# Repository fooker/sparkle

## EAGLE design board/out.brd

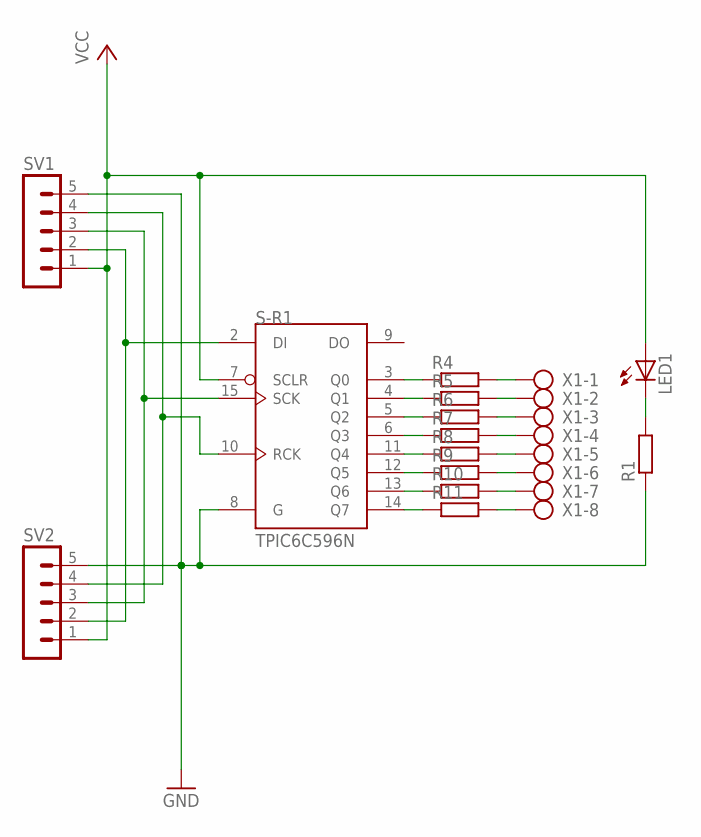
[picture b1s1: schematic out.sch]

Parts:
LED1: LED3MM
R1, R4, R5, R6, R7, R8, R9, R10, R11: R-EU_0207/2V; 0207/2V
S-R1: TPIC6C596N; DIL16
SV1, SV2: MA05-1
X1: AK500/8-H

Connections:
GND: R1.1, S-R1.8 (G), S-R1.16 (GND), SV1.5, SV2.5
unnamed: LED1.K (C), R1.2
unnamed: S-R1.2 (DI), SV1.2, SV2.2
unnamed: S-R1.10 (RCK), SV1.4, SV2.4
unnamed: S-R1.15 (SCK), SV1.3, SV2.3
unnamed: R4.1, S-R1.3 (Q0)
unnamed: R5.1, S-R1.4 (Q1)
unnamed: R6.1, S-R1.5 (Q2)
unnamed: R7.1, S-R1.6 (Q3)
unnamed: R8.1, S-R1.11 (Q4)
unnamed: R9.1, S-R1.12 (Q5)
unnamed: R10.1, S-R1.13 (Q6)
unnamed: R11.1, S-R1.14 (Q7)
unnamed: R4.2, X1.1
unnamed: R5.2, X1.2
unnamed: R6.2, X1.3
unnamed: R7.2, X1.4
unnamed: R8.2, X1.5
unnamed: R9.2, X1.6
unnamed: R10.2, X1.7
unnamed: R11.2, X1.8
VCC: LED1.A, S-R1.1 (VCC), S-R1.7 (SCLR), SV1.1, SV2.1

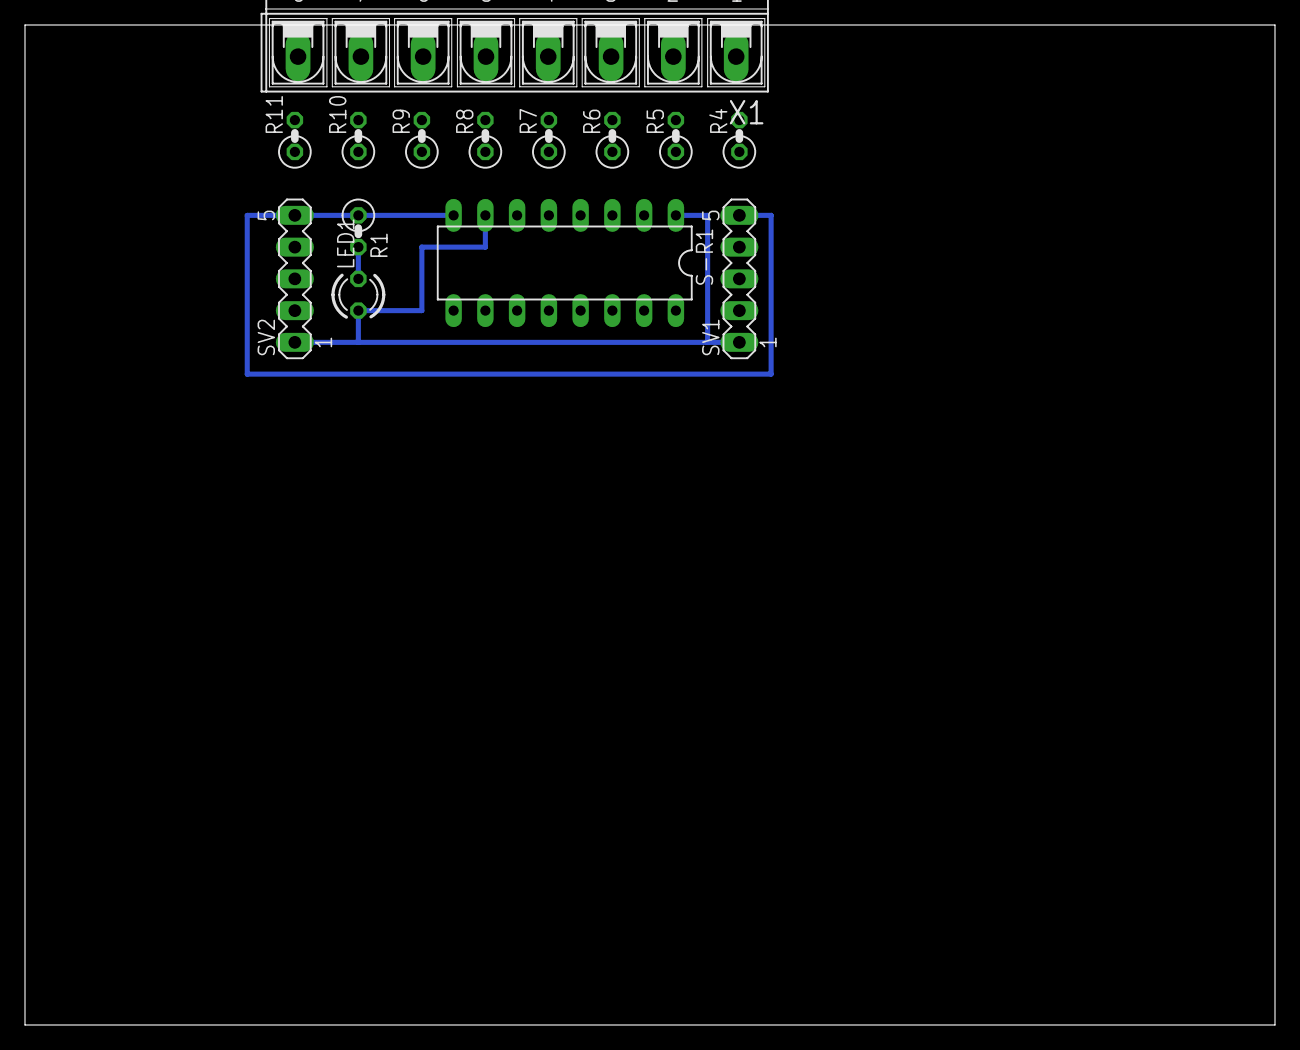
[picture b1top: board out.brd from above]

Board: 2 copper layers, 100.0 x 80.0 mm, 14 parts (0 on the bottom side), 22 nets.

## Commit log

2014-02-24 Single LED version
2014-03-21 Schematics added
2014-03-21 Improved PWM timing
2014-05-07 More optimisation
2014-05-10 Lalala
2014-05-13 Added i2c functions
2014-05-18 Fixed ordering on I2C commands to be RGB
2014-05-18 Python library added for controlling
2014-05-18 Animation 'white light' added
2014-05-18 Animation 'rainbow' added
